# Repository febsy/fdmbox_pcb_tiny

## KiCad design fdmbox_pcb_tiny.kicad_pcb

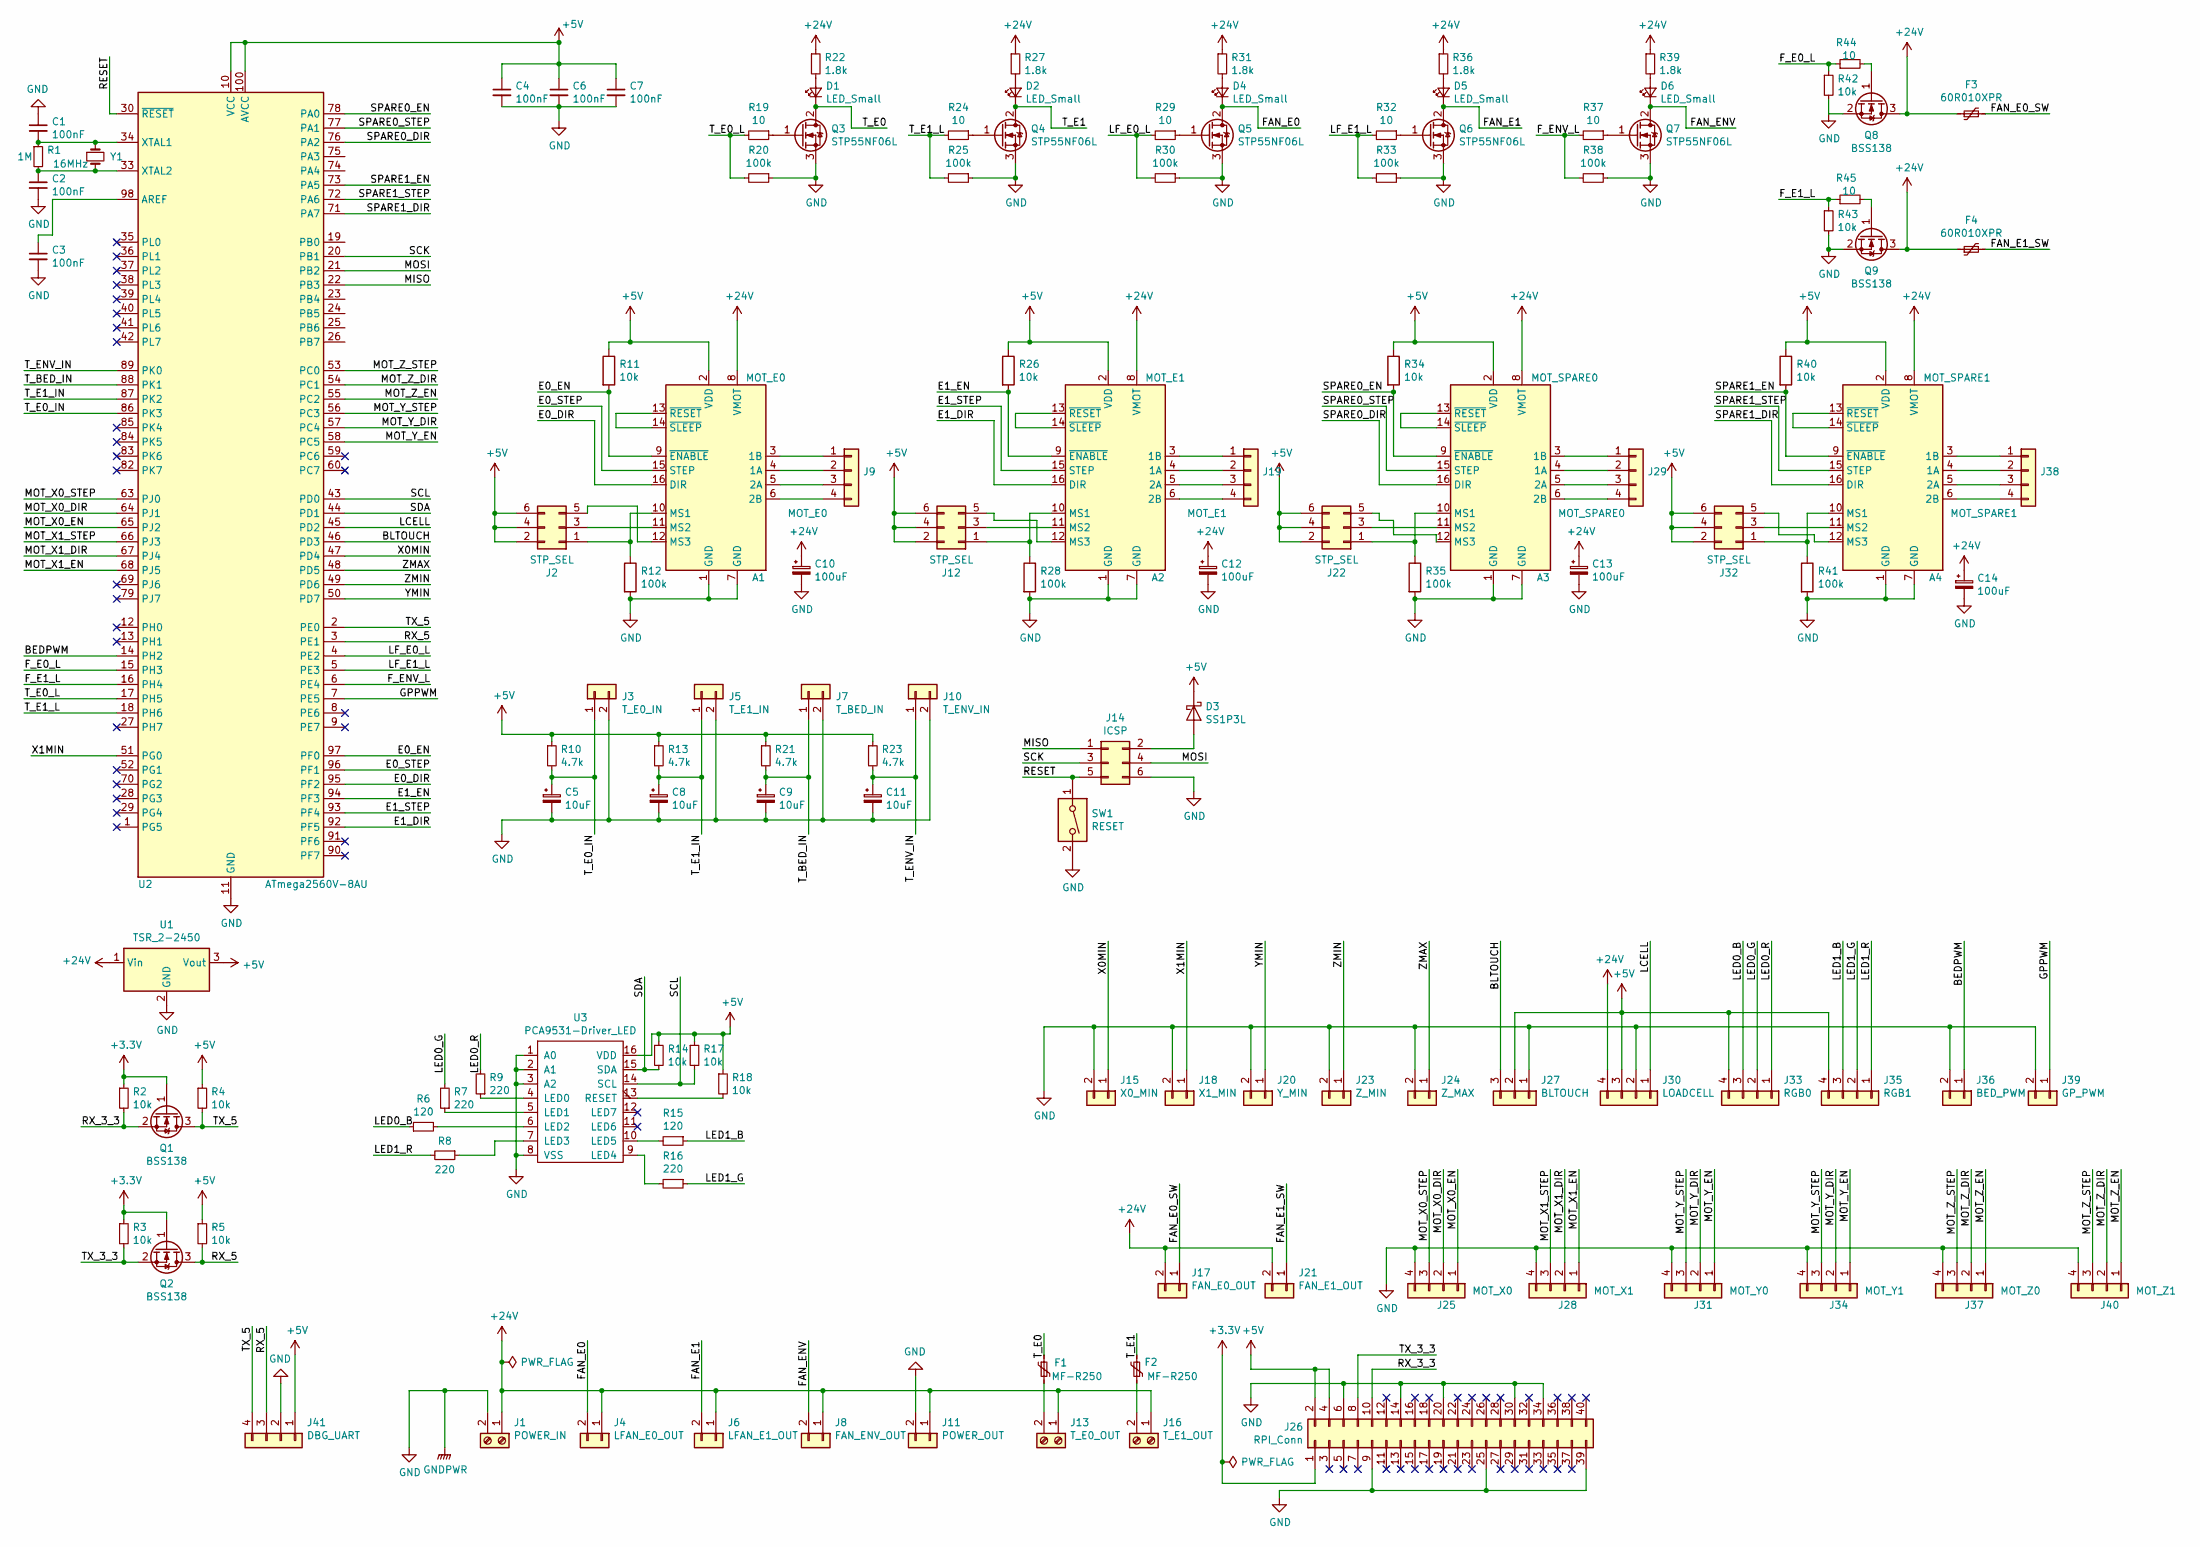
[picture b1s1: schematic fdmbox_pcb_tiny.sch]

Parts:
A1: MOT_E0; Pololu_Breakout-16_15.2x20.3mm
A2: MOT_E1; Pololu_Breakout-16_15.2x20.3mm
A3: MOT_SPARE0; Pololu_Breakout-16_15.2x20.3mm
A4: MOT_SPARE1; Pololu_Breakout-16_15.2x20.3mm
C1, C2, C3, C4, C6, C7: 100nF; C_0805_2012Metric_Pad1.15x1.40mm_HandSolder
C5, C8, C9, C11: 10uF; CP_Elec_5x5.4
C10, C12, C13, C14: 100uF; CP_Elec_8x6.2
D1, D2, D4, D5, D6: LED_Small; LED_0805_2012Metric_Pad1.15x1.40mm_HandSolder
D3: SS1P3L; DO-220AA
F1, F2: MF-R250; C_Disc_D5.1mm_W3.2mm_P5.00mm
F3, F4: 60R010XPR; C_Rect_L11.0mm_W5.1mm_P10.00mm_MKT
J1: POWER_IN; TerminalBlock_RND_205-00287_1x02_P5.08mm_Horizontal
J2, J12, J22, J32: STP_SEL; PinHeader_2x03_P2.54mm_Vertical
J3: T_E0_IN; JST_XH_B02B-XH-AM_1x02_P2.50mm_Vertical
J4: LFAN_E0_OUT; JST_XH_B02B-XH-AM_1x02_P2.50mm_Vertical
J5: T_E1_IN; JST_XH_B02B-XH-AM_1x02_P2.50mm_Vertical
J6: LFAN_E1_OUT; JST_XH_B02B-XH-AM_1x02_P2.50mm_Vertical
J7: T_BED_IN; JST_XH_B02B-XH-AM_1x02_P2.50mm_Vertical
J8: FAN_ENV_OUT; JST_XH_B02B-XH-AM_1x02_P2.50mm_Vertical
J9: MOT_E0; JST_XH_B04B-XH-AM_1x04_P2.50mm_Vertical
J10: T_ENV_IN; JST_XH_B02B-XH-AM_1x02_P2.50mm_Vertical
J11: POWER_OUT; JST_XH_B02B-XH-AM_1x02_P2.50mm_Vertical
J13: T_E0_OUT; TerminalBlock_RND_205-00287_1x02_P5.08mm_Horizontal
J14: ICSP; PinSocket_2x03_P2.54mm_Vertical
J15: X0_MIN; JST_XH_B02B-XH-AM_1x02_P2.50mm_Vertical
J16: T_E1_OUT; TerminalBlock_RND_205-00287_1x02_P5.08mm_Horizontal
J17: FAN_E0_OUT; JST_XH_B02B-XH-AM_1x02_P2.50mm_Vertical
J18: X1_MIN; JST_XH_B02B-XH-AM_1x02_P2.50mm_Vertical
J19: MOT_E1; JST_XH_B04B-XH-AM_1x04_P2.50mm_Vertical
J20: Y_MIN; JST_XH_B02B-XH-AM_1x02_P2.50mm_Vertical
J21: FAN_E1_OUT; JST_XH_B02B-XH-AM_1x02_P2.50mm_Vertical
J23: Z_MIN; JST_XH_B02B-XH-AM_1x02_P2.50mm_Vertical
J24: Z_MAX; JST_XH_B02B-XH-AM_1x02_P2.50mm_Vertical
J25: MOT_X0; JST_XH_B04B-XH-AM_1x04_P2.50mm_Vertical
J26: RPI_Conn; PinHeader_2x20_P2.54mm_Vertical
J27: BLTOUCH; JST_XH_B03B-XH-AM_1x03_P2.50mm_Vertical
J28: MOT_X1; JST_XH_B04B-XH-AM_1x04_P2.50mm_Vertical
J29: MOT_SPARE0; JST_XH_B04B-XH-AM_1x04_P2.50mm_Vertical
J30: LOADCELL; JST_XH_B04B-XH-AM_1x04_P2.50mm_Vertical
J31: MOT_Y0; JST_XH_B04B-XH-AM_1x04_P2.50mm_Vertical
J33: RGB0; JST_XH_B04B-XH-AM_1x04_P2.50mm_Vertical
J34: MOT_Y1; JST_XH_B04B-XH-AM_1x04_P2.50mm_Vertical
J35: RGB1; JST_XH_B04B-XH-AM_1x04_P2.50mm_Vertical
J36: BED_PWM; JST_XH_B02B-XH-AM_1x02_P2.50mm_Vertical
J37: MOT_Z0; JST_XH_B04B-XH-AM_1x04_P2.50mm_Vertical
J38: MOT_SPARE1; JST_XH_B04B-XH-AM_1x04_P2.50mm_Vertical
J39: GP_PWM; JST_XH_B02B-XH-AM_1x02_P2.50mm_Vertical
J40: MOT_Z1; JST_XH_B04B-XH-AM_1x04_P2.50mm_Vertical
J41: DBG_UART; PinSocket_1x04_P2.54mm_Vertical
Q1, Q2, Q8, Q9: BSS138; SOT-23
Q3, Q4, Q5, Q6, Q7: STP55NF06L; TO-220-3_Vertical
R1: 1M; R_0805_2012Metric_Pad1.15x1.40mm_HandSolder
R2, R3, R4, R5, R11, R14, R17, R18, R26, R34, R40, R42, R43: 10k; R_0805_2012Metric_Pad1.15x1.40mm_HandSolder
R6, R15: 120; R_0805_2012Metric_Pad1.15x1.40mm_HandSolder
R7, R8, R9, R16: 220; R_0805_2012Metric_Pad1.15x1.40mm_HandSolder
R10, R13, R21, R23: 4.7k; R_0805_2012Metric_Pad1.15x1.40mm_HandSolder
R12, R20, R25, R28, R30, R33, R35, R38, R41: 100k; R_0805_2012Metric_Pad1.15x1.40mm_HandSolder
R19, R24, R29, R32, R37, R44, R45: 10; R_0805_2012Metric_Pad1.15x1.40mm_HandSolder
R22, R27, R31, R36, R39: 1.8k; R_0805_2012Metric_Pad1.15x1.40mm_HandSolder
SW1: RESET; SW_Tactile_Straight_KSL0Axx1LFTR
U1: TSR_2-2450; Converter_DCDC_TRACO_TSR-1_THT
U2: ATmega2560V-8AU; TQFP-100_14x14mm_P0.5mm
U3: PCA9531-Driver_LED; TSSOP-16_4.4x5mm_P0.65mm
Y1: 16MHz; Crystal_HC49-U_Vertical

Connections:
+3V3: J26.1, Q1.1 (G), Q2.1 (G), R2.1, R3.1
+5V: A1.2 (VDD), A2.2 (VDD), A3.2 (VDD), A4.2 (VDD), C4.1, C6.1, C7.1, D3.1 (K), J2.2, J2.4, J2.6, J12.2, J12.4, J12.6, J22.2, J22.4, J22.6, J26.2, J26.4, J27.2, J30.3, J32.2, J32.4, J32.6, J33.4, J35.4, J41.1, R4.1, R5.1, R10.1, R11.1, R13.1, R14.1, R17.1, R18.1, R21.1, R23.1, R26.1, R34.1, R40.1, U1.3 (Vout), U2.10 (VCC), U2.31 (VCC), U2.61 (VCC), U2.80 (VCC), U2.100 (AVCC), U3.16 (VDD)
+24V: A1.8 (VMOT), A2.8 (VMOT), A3.8 (VMOT), A4.8 (VMOT), C10.1, C12.1, C13.1, C14.1, F3.1, F4.1, J1.1, J4.1, J6.1, J8.1, J11.1, J13.1, J16.1, J17.2, J21.2, J30.4, Q8.3 (D), Q9.3 (D), R22.1, R27.1, R31.1, R36.1, R39.1, U1.1 (Vin)
/BEDPWM: J36.1, U2.14 (PH2)
/BLTOUCH: J27.3, U2.46 (PD3)
/E0_DIR: A1.16 (DIR), U2.95 (PF2)
/E0_EN: A1.9 (~ENABLE), R11.2, U2.97 (PF0)
/E0_STEP: A1.15 (STEP), U2.96 (PF1)
/E1_DIR: A2.16 (DIR), U2.92 (PF5)
/E1_EN: A2.9 (~ENABLE), R26.2, U2.94 (PF3)
/E1_STEP: A2.15 (STEP), U2.93 (PF4)
/FAN_E0: D4.1 (K), J4.2, Q5.2 (D)
/FAN_E0_SW: F3.2, J17.1
/FAN_E1: D5.1 (K), J6.2, Q6.2 (D)
/FAN_E1_SW: F4.2, J21.1
/FAN_ENV: D6.1 (K), J8.2, Q7.2 (D)
/F_E0_L: R42.1, R44.1, U2.15 (PH3)
/F_E1_L: R43.1, R45.1, U2.16 (PH4)
/F_ENV_L: R37.2, R38.2, U2.6 (PE4)
/GPPWM: J39.1, U2.7 (PE5)
/LCELL: J30.1, U2.45 (PD2)
/LED0_B: J33.3, R6.1
/LED0_G: J33.2, R7.2
/LED0_R: J33.1, R9.2
/LED1_B: J35.3, R15.1
/LED1_G: J35.2, R16.1
/LED1_R: J35.1, R8.2
/LF_E0_L: R29.2, R30.2, U2.4 (PE2)
/LF_E1_L: R32.2, R33.2, U2.5 (PE3)
/MISO: J14.1, U2.22 (PB3)
/MOSI: J14.4, U2.21 (PB2)
/MOT_X0_DIR: J25.2, U2.64 (PJ1)
/MOT_X0_EN: J25.1, U2.65 (PJ2)
/MOT_X0_STEP: J25.3, U2.63 (PJ0)
/MOT_X1_DIR: J28.2, U2.67 (PJ4)
/MOT_X1_EN: J28.1, U2.68 (PJ5)
/MOT_X1_STEP: J28.3, U2.66 (PJ3)
/MOT_Y_DIR: J31.2, J34.2, U2.57 (PC4)
/MOT_Y_EN: J31.1, J34.1, U2.58 (PC5)
/MOT_Y_STEP: J31.3, J34.3, U2.56 (PC3)
/MOT_Z_DIR: J37.2, J40.2, U2.54 (PC1)
/MOT_Z_EN: J37.1, J40.1, U2.55 (PC2)
/MOT_Z_STEP: J37.3, J40.3, U2.53 (PC0)
/RESET: J14.5, SW1.1, U2.30 (~RESET)
/RX_3_3: J26.10, Q1.2 (S), R2.2
/RX_5: J41.3, Q2.3 (D), R5.2, U2.3 (PE1)
/SCK: J14.3, U2.20 (PB1)
/SCL: R17.2, U2.43 (PD0), U3.14 (SCL)
/SDA: R14.2, U2.44 (PD1), U3.15 (SDA)
/SPARE0_DIR: A3.16 (DIR), U2.76 (PA2)
/SPARE0_EN: A3.9 (~ENABLE), R34.2, U2.78 (PA0)
/SPARE0_STEP: A3.15 (STEP), U2.77 (PA1)
/SPARE1_DIR: A4.16 (DIR), U2.71 (PA7)
/SPARE1_EN: A4.9 (~ENABLE), R40.2, U2.73 (PA5)
/SPARE1_STEP: A4.15 (STEP), U2.72 (PA6)
/TX_3_3: J26.8, Q2.2 (S), R3.2
/TX_5: J41.4, Q1.3 (D), R4.2, U2.2 (PE0)
/T_BED_IN: C9.1, J7.1, R21.2, U2.88 (PK1)
/T_E0: D1.1 (K), F1.1, Q3.2 (D)
/T_E0_IN: C5.1, J3.1, R10.2, U2.86 (PK3)
/T_E0_L: R19.2, R20.2, U2.17 (PH5)
/T_E1: D2.1 (K), F2.2, Q4.2 (D)
/T_E1_IN: C8.1, J5.1, R13.2, U2.87 (PK2)
/T_E1_L: R24.2, R25.2, U2.18 (PH6)
/T_ENV_IN: C11.1, J10.1, R23.2, U2.89 (PK0)
/X0MIN: J15.1, U2.47 (PD4)
/X1MIN: J18.1, U2.51 (PG0)
/YMIN: J20.1, U2.50 (PD7)
/ZMAX: J24.1, U2.48 (PD5)
/ZMIN: J23.1, U2.49 (PD6)
GND: A1.1 (GND), A1.7 (GND), A2.1 (GND), A2.7 (GND), A3.1 (GND), A3.7 (GND), A4.1 (GND), A4.7 (GND), C1.1, C2.2, C3.2, C4.2, C5.2, C6.2, C7.2, C8.2, C9.2, C10.2, C11.2, C12.2, C13.2, C14.2, J1.2, J3.2, J5.2, J7.2, J10.2, J11.2, J14.6, J15.2, J18.2, J20.2, J23.2, J24.2, J25.4, J26.6, J26.9, J26.14, J26.20, J26.25, J26.30, J26.34, J26.39, J27.1, J28.4, J30.2, J31.4, J34.4, J36.2, J37.4, J39.2, J40.4, J41.2, Q3.3 (S), Q4.3 (S), Q5.3 (S), Q6.3 (S), Q7.3 (S), Q8.2 (S), Q9.2 (S), R12.2, R20.1, R25.1, R28.2, R30.1, R33.1, R35.2, R38.1, R41.2, R42.2, R43.2, SW1.2, U1.2 (GND), U2.11 (GND), U2.32 (GND), U2.62 (GND), U2.81 (GND), U2.99 (GND), U3.1 (A0), U3.2 (A1), U3.3 (A2), U3.8 (VSS)
unnamed: A1.3 (1B), J9.1
unnamed: A1.4 (1A), J9.2
unnamed: A1.5 (2A), J9.3
unnamed: A1.6 (2B), J9.4
unnamed: A1.10 (MS1), J2.1, R12.1
unnamed: A1.11 (MS2), J2.3
unnamed: A1.12 (MS3), J2.5
unnamed: A1.13 (~RESET), A1.14 (~SLEEP)
unnamed: A2.3 (1B), J19.1
unnamed: A2.4 (1A), J19.2
unnamed: A2.5 (2A), J19.3
unnamed: A2.6 (2B), J19.4
unnamed: A2.10 (MS1), J12.1, R28.1
unnamed: A2.11 (MS2), J12.3
unnamed: A2.12 (MS3), J12.5
unnamed: A2.13 (~RESET), A2.14 (~SLEEP)
unnamed: A3.3 (1B), J29.1
unnamed: A3.4 (1A), J29.2
unnamed: A3.5 (2A), J29.3
unnamed: A3.6 (2B), J29.4
unnamed: A3.10 (MS1), J22.1, R35.1
unnamed: A3.11 (MS2), J22.3
unnamed: A3.12 (MS3), J22.5
unnamed: A3.13 (~RESET), A3.14 (~SLEEP)
unnamed: A4.3 (1B), J38.1
unnamed: A4.4 (1A), J38.2
unnamed: A4.5 (2A), J38.3
unnamed: A4.6 (2B), J38.4
unnamed: A4.10 (MS1), J32.1, R41.1
unnamed: A4.11 (MS2), J32.3
unnamed: A4.12 (MS3), J32.5
unnamed: A4.13 (~RESET), A4.14 (~SLEEP)
unnamed: C1.2, R1.1, U2.34 (XTAL1), Y1.1
unnamed: C2.1, R1.2, U2.33 (XTAL2), Y1.2
unnamed: C3.1, U2.98 (AREF)
unnamed: D1.2 (A), R22.2
unnamed: D2.2 (A), R27.2
unnamed: D3.2 (A), J14.2
unnamed: D4.2 (A), R31.2
unnamed: D5.2 (A), R36.2
unnamed: D6.2 (A), R39.2
unnamed: F1.2, J13.2
unnamed: F2.1, J16.2
unnamed: Q3.1 (G), R19.1
unnamed: Q4.1 (G), R24.1
unnamed: Q5.1 (G), R29.1
unnamed: Q6.1 (G), R32.1
unnamed: Q7.1 (G), R37.1
unnamed: Q8.1 (G), R44.2
unnamed: Q9.1 (G), R45.2
unnamed: R6.2, U3.6 (LED2)
unnamed: R7.1, U3.5 (LED1)
unnamed: R8.1, U3.7 (LED3)
unnamed: R9.1, U3.4 (LED0)
unnamed: R15.2, U3.10 (LED5)
unnamed: R16.2, U3.9 (LED4)
unnamed: R18.2, U3.13 (RESET)

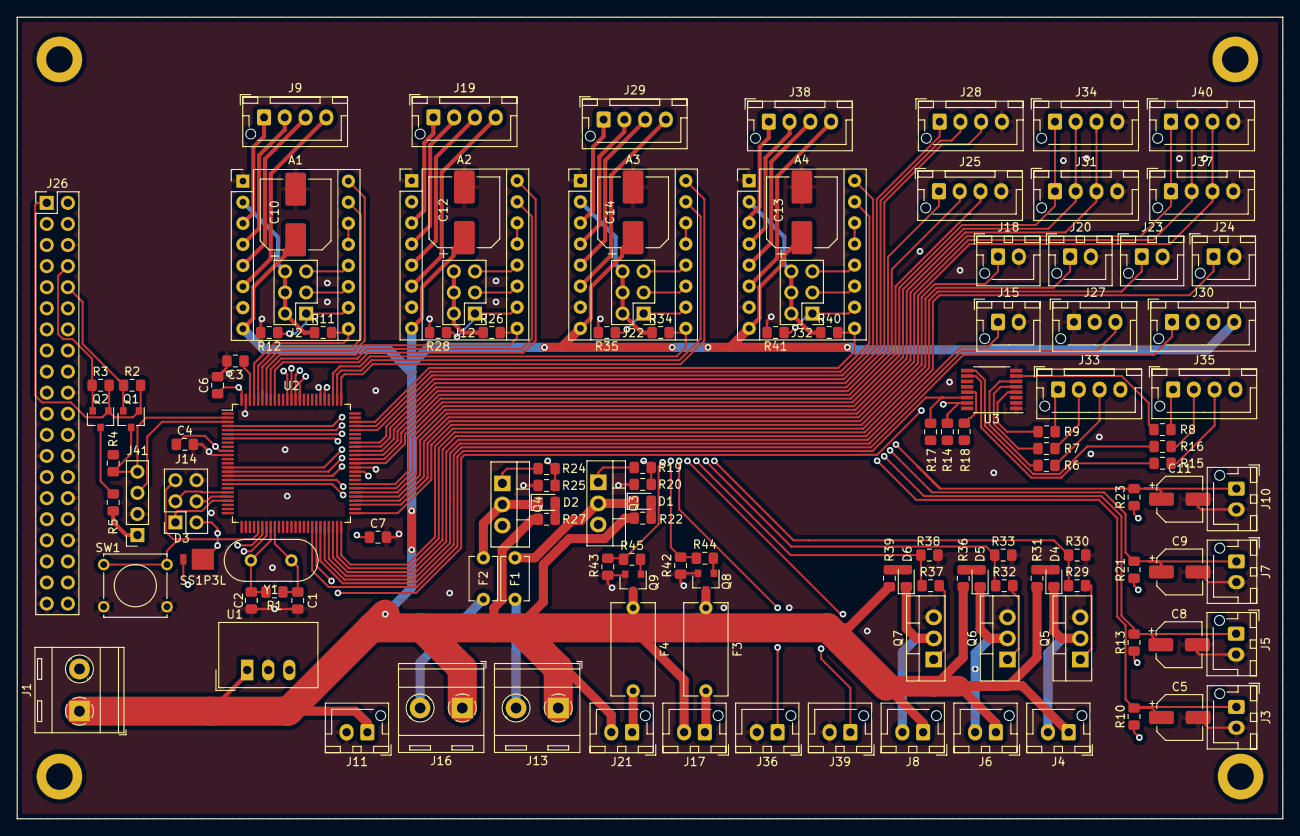
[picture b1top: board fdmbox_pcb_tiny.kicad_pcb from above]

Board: 4 copper layers, 152.4 x 96.5 mm, 128 parts (0 on the bottom side), 128 nets.

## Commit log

2019-03-02 Added connections to MCU
2019-03-03 added footprints to schematics, started pcb layout
2019-03-10 PCB finished -so far..
